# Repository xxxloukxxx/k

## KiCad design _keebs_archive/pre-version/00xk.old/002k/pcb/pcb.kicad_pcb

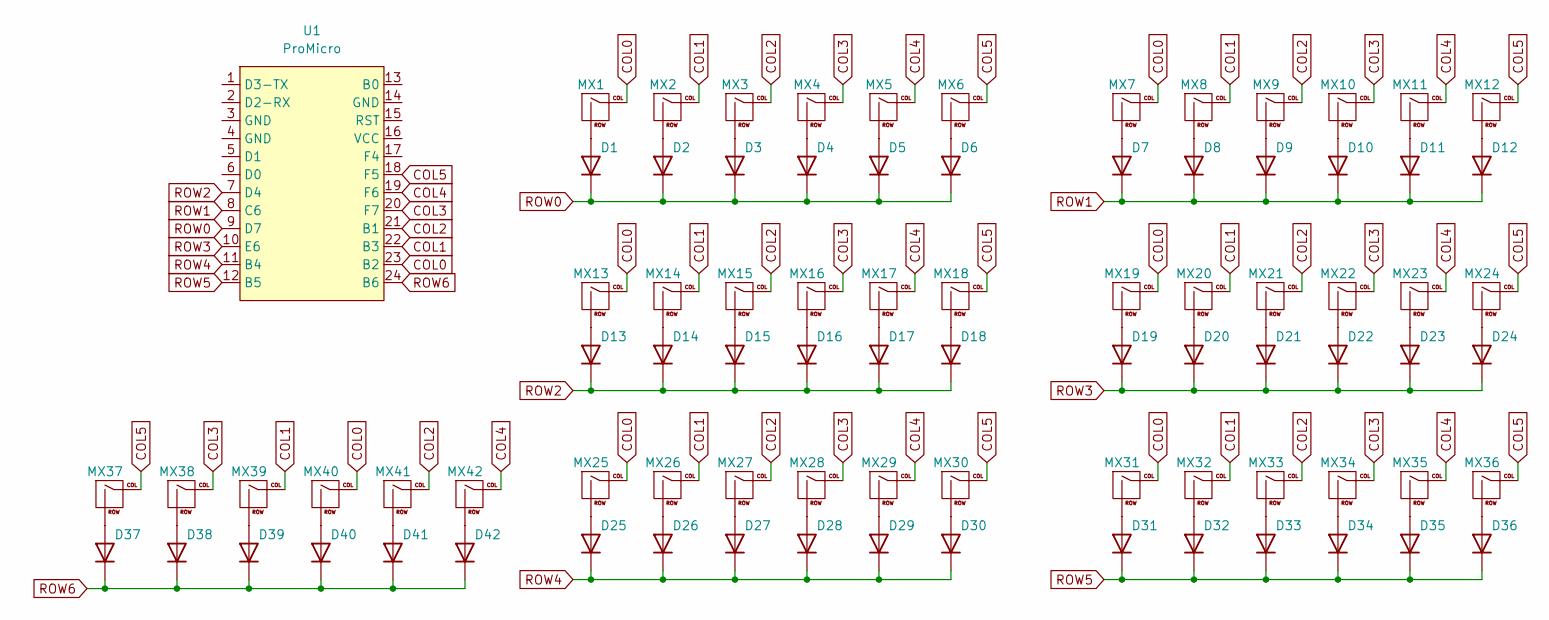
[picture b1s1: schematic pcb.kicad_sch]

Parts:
D1, D2, D3, D4, D5, D6, D7, D8, D9, D10, D11, D12, D13, D14, D15, D16, D17, D18, D19, D20, D21, D22, D23, D24, D25, D26, D27, D28, D29, D30, D31, D32, D33, D34, D35, D36, D37, D38, D39, D40, D41, D42: 1N4148; D_DO-35_SOD27_P7.62mm_Horizontal
MX1, MX2, MX3, MX4, MX5, MX6, MX7, MX8, MX9, MX10, MX11, MX12, MX13, MX14, MX15, MX16, MX17, MX18, MX19, MX20, MX21, MX22, MX23, MX24, MX25, MX26, MX27, MX28, MX29, MX30, MX31, MX32, MX33, MX34, MX35, MX36, MX37, MX42: MX; MX-Solderable-1U
MX38, MX39, MX40, MX41: MX; MX-Solderable-1.5U
U1: ProMicro; ProMicro_USBup

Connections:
COL0: MX1.1 (COL), MX7.1 (COL), MX13.1 (COL), MX19.1 (COL), MX25.1 (COL), MX31.1 (COL), MX40.1 (COL), U1.23 (B2)
COL1: MX2.1 (COL), MX8.1 (COL), MX14.1 (COL), MX20.1 (COL), MX26.1 (COL), MX32.1 (COL), MX39.1 (COL), U1.22 (B3)
COL2: MX3.1 (COL), MX9.1 (COL), MX15.1 (COL), MX21.1 (COL), MX27.1 (COL), MX33.1 (COL), MX41.1 (COL), U1.21 (B1)
COL3: MX4.1 (COL), MX10.1 (COL), MX16.1 (COL), MX22.1 (COL), MX28.1 (COL), MX34.1 (COL), MX38.1 (COL), U1.20 (F7)
COL4: MX5.1 (COL), MX11.1 (COL), MX17.1 (COL), MX23.1 (COL), MX29.1 (COL), MX35.1 (COL), MX42.1 (COL), U1.19 (F6)
COL5: MX6.1 (COL), MX12.1 (COL), MX18.1 (COL), MX24.1 (COL), MX30.1 (COL), MX36.1 (COL), MX37.1 (COL), U1.18 (F5)
unnamed: D1.2 (A), MX1.2 (ROW)
unnamed: D2.2 (A), MX2.2 (ROW)
unnamed: D3.2 (A), MX3.2 (ROW)
unnamed: D4.2 (A), MX4.2 (ROW)
unnamed: D5.2 (A), MX5.2 (ROW)
unnamed: D6.2 (A), MX6.2 (ROW)
unnamed: D7.2 (A), MX7.2 (ROW)
unnamed: D8.2 (A), MX8.2 (ROW)
unnamed: D9.2 (A), MX9.2 (ROW)
unnamed: D10.2 (A), MX10.2 (ROW)
unnamed: D11.2 (A), MX11.2 (ROW)
unnamed: D12.2 (A), MX12.2 (ROW)
unnamed: D13.2 (A), MX13.2 (ROW)
unnamed: D14.2 (A), MX14.2 (ROW)
unnamed: D15.2 (A), MX15.2 (ROW)
unnamed: D16.2 (A), MX16.2 (ROW)
unnamed: D17.2 (A), MX17.2 (ROW)
unnamed: D18.2 (A), MX18.2 (ROW)
unnamed: D19.2 (A), MX19.2 (ROW)
unnamed: D20.2 (A), MX20.2 (ROW)
unnamed: D21.2 (A), MX21.2 (ROW)
unnamed: D22.2 (A), MX22.2 (ROW)
unnamed: D23.2 (A), MX23.2 (ROW)
unnamed: D24.2 (A), MX24.2 (ROW)
unnamed: D25.2 (A), MX25.2 (ROW)
unnamed: D26.2 (A), MX26.2 (ROW)
unnamed: D27.2 (A), MX27.2 (ROW)
unnamed: D28.2 (A), MX28.2 (ROW)
unnamed: D29.2 (A), MX29.2 (ROW)
unnamed: D30.2 (A), MX30.2 (ROW)
unnamed: D31.2 (A), MX31.2 (ROW)
unnamed: D32.2 (A), MX32.2 (ROW)
unnamed: D33.2 (A), MX33.2 (ROW)
unnamed: D34.2 (A), MX34.2 (ROW)
unnamed: D35.2 (A), MX35.2 (ROW)
unnamed: D36.2 (A), MX36.2 (ROW)
unnamed: D37.2 (A), MX37.2 (ROW)
unnamed: D38.2 (A), MX38.2 (ROW)
unnamed: D39.2 (A), MX39.2 (ROW)
unnamed: D40.2 (A), MX40.2 (ROW)
unnamed: D41.2 (A), MX41.2 (ROW)
unnamed: D42.2 (A), MX42.2 (ROW)
ROW0: D1.1 (K), D2.1 (K), D3.1 (K), D4.1 (K), D5.1 (K), D6.1 (K), U1.9 (D7)
ROW1: D7.1 (K), D8.1 (K), D9.1 (K), D10.1 (K), D11.1 (K), D12.1 (K), U1.8 (C6)
ROW2: D13.1 (K), D14.1 (K), D15.1 (K), D16.1 (K), D17.1 (K), D18.1 (K), U1.7 (D4)
ROW3: D19.1 (K), D20.1 (K), D21.1 (K), D22.1 (K), D23.1 (K), D24.1 (K), U1.10 (E6)
ROW4: D25.1 (K), D26.1 (K), D27.1 (K), D28.1 (K), D29.1 (K), D30.1 (K), U1.11 (B4)
ROW5: D31.1 (K), D32.1 (K), D33.1 (K), D34.1 (K), D35.1 (K), D36.1 (K), U1.12 (B5)
ROW6: D37.1 (K), D38.1 (K), D39.1 (K), D40.1 (K), D41.1 (K), D42.1 (K), U1.24 (B6)

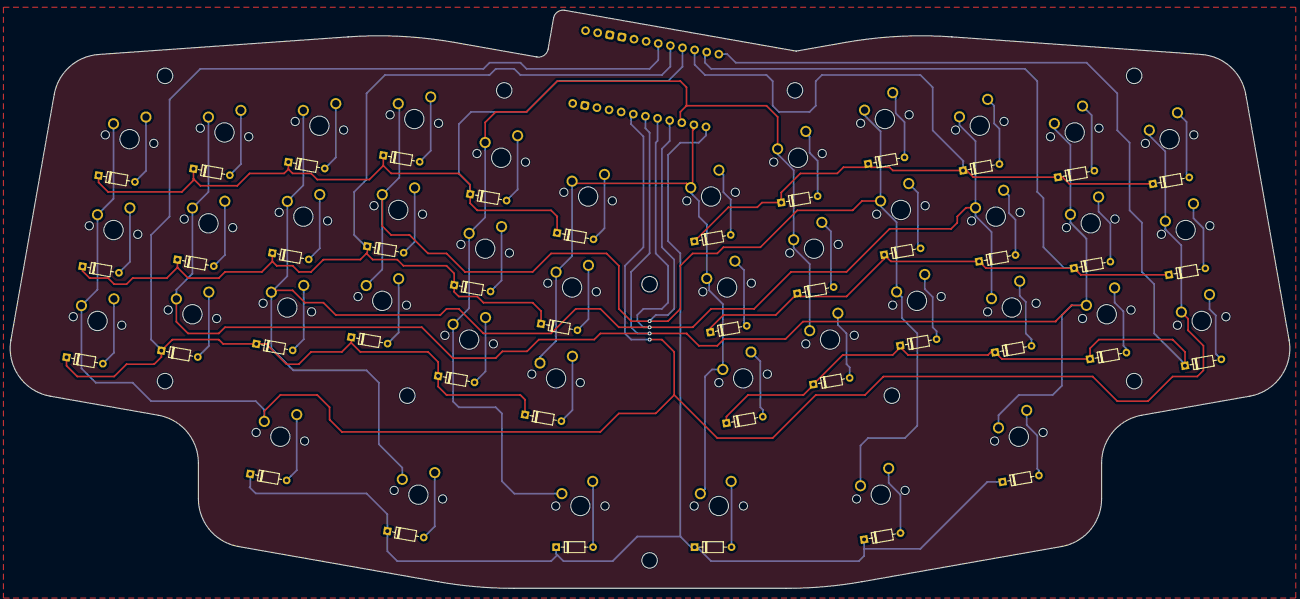
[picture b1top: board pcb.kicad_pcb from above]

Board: 2 copper layers, 264.1 x 119.3 mm, 95 parts (1 on the bottom side), 55 nets.

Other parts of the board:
REF01, REF02, REF03, REF04, REF05, REF06, REF07, REF08, REF09, REF10: MountingHole_3.2mm_M3

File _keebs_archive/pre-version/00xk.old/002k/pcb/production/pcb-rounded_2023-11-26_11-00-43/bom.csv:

Designator,Footprint,Quantity,Value,LCSC Part #
"D1, D10, D11, D12, D13, D14, D15, D16, D17, D18, D19, D2, D20, D21, D22, D23, D24, D25, D26, D27, D28, D29, D3, D30, D31, D32, D33, D34, D35, D36, D37, D38, D39, D4, D40, D41, D42, D5, D6, D7, D8, D9",D_DO-35_SOD27_P7.62mm_Horizontal,42,1N4148,
"MX1, MX10, MX11, MX12, MX13, MX14, MX15, MX16, MX17, MX18, MX19, MX2, MX20, MX21, MX22, MX23, MX24, MX25, MX26, MX27, MX28, MX29, MX3, MX30, MX31, MX32, MX33, MX34, MX35, MX36, MX37, MX4, MX42, MX5, MX6, MX7, MX8, MX9",MX-Solderable-1U,38,MX,
"MX38, MX39, MX40, MX41",MX-Solderable-1.5U,4,MX,

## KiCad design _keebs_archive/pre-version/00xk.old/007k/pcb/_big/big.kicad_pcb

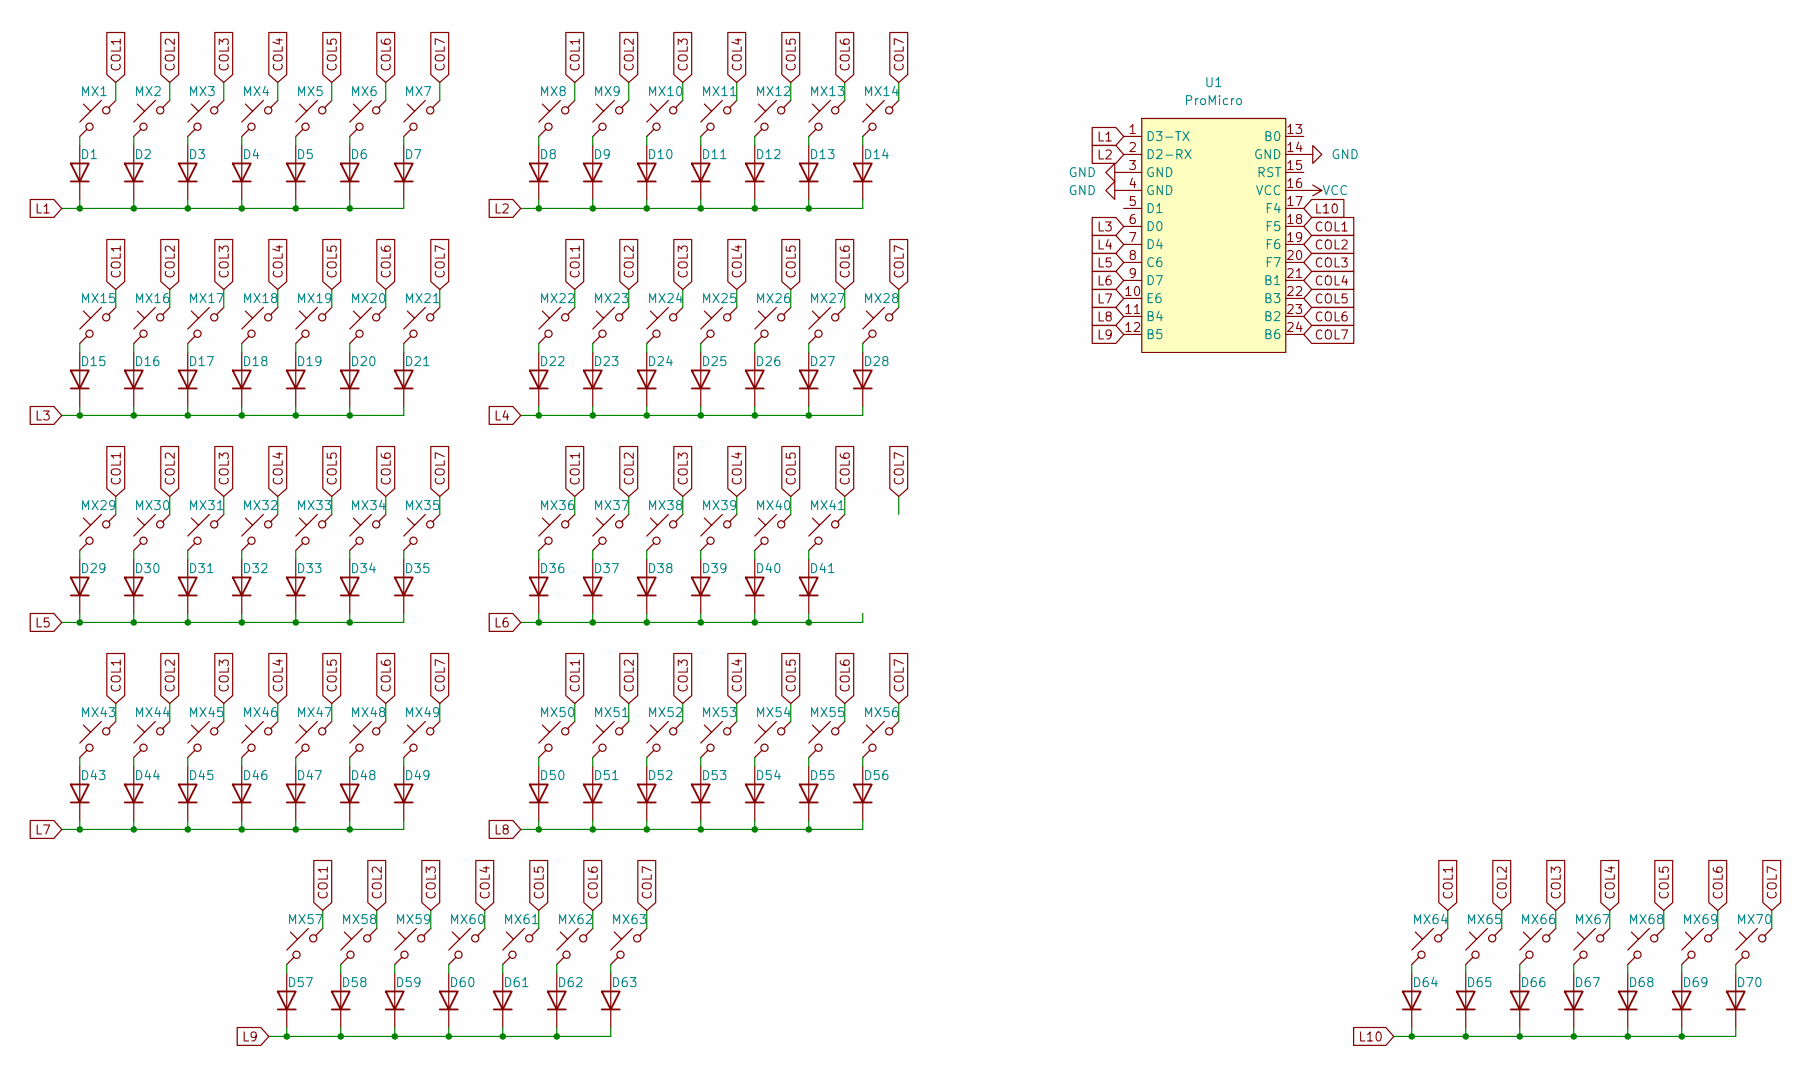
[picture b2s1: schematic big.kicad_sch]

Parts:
D1, D2, D3, D4, D5, D6, D7, D8, D9, D10, D11, D12, D13, D14, D15, D16, D17, D18, D19, D20, D21, D22, D23, D24, D25, D26, D27, D28, D29, D30, D31, D32, D33, D34, D35, D36, D37, D38, D39, D40, D41, D43, D44, D45, D46, D47, D48, D49, D50, D51, D52, D53, D54, D55, D56, D57, D58, D59, D60, D61, D62, D63, D64, D65, D66, D67, D68, D69, D70: 1N4148; D_DO-35_SOD27_P7.62mm_Horizontal
MX1, MX2, MX3, MX4, MX5, MX6, MX7, MX8, MX9, MX10, MX11, MX12, MX13, MX16, MX17, MX18, MX19, MX20, MX21, MX22, MX23, MX24, MX25, MX26, MX27, MX28, MX30, MX31, MX32, MX33, MX34, MX35, MX36, MX37, MX38, MX39, MX40, MX44, MX45, MX46, MX47, MX48, MX49, MX50, MX51, MX52, MX53, MX55, MX56, MX63, MX64, MX65, MX66, MX67, MX68, MX69, MX70: MX_SW_solder; MX-Alps-Hybrid-1U
MX14, MX15: MX_SW_solder; MX-Alps-Hybrid-1.5U
MX29, MX41, MX54: MX_SW_solder; MX-Alps-Hybrid-1.75U
MX43, MX62: MX_SW_solder; MX-Alps-Hybrid-2.25U
MX57, MX58, MX59, MX61: MX_SW_solder; MX-Alps-Hybrid-1.25U
MX60: MX_SW_solder; MX-Alps-Hybrid-2.75U
U1: ProMicro; ProMicro_USBup

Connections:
COL1: MX1.2, MX8.2, MX15.2, MX22.2, MX29.2, MX36.2, MX43.2, MX50.2, MX57.2, MX64.2, U1.18 (F5)
COL2: MX2.2, MX9.2, MX16.2, MX23.2, MX30.2, MX37.2, MX44.2, MX51.2, MX58.2, MX65.2, U1.19 (F6)
COL3: MX3.2, MX10.2, MX17.2, MX24.2, MX31.2, MX38.2, MX45.2, MX52.2, MX59.2, MX66.2, U1.20 (F7)
COL4: MX4.2, MX11.2, MX18.2, MX25.2, MX32.2, MX39.2, MX46.2, MX53.2, MX60.2, MX67.2, U1.21 (B1)
COL5: MX5.2, MX12.2, MX19.2, MX26.2, MX33.2, MX40.2, MX47.2, MX54.2, MX61.2, MX68.2, U1.22 (B3)
COL6: MX6.2, MX13.2, MX20.2, MX27.2, MX34.2, MX41.2, MX48.2, MX55.2, MX62.2, MX69.2, U1.23 (B2)
COL7: MX7.2, MX14.2, MX21.2, MX28.2, MX35.2, MX49.2, MX56.2, MX63.2, MX70.2, U1.24 (B6)
GND: U1.3 (GND), U1.4 (GND), U1.14 (GND)
L1: D1.1 (K), D2.1 (K), D3.1 (K), D4.1 (K), D5.1 (K), D6.1 (K), D7.1 (K), U1.1 (D3-TX)
L2: D8.1 (K), D9.1 (K), D10.1 (K), D11.1 (K), D12.1 (K), D13.1 (K), D14.1 (K), U1.2 (D2-RX)
L3: D15.1 (K), D16.1 (K), D17.1 (K), D18.1 (K), D19.1 (K), D20.1 (K), D21.1 (K), U1.6 (D0)
L4: D22.1 (K), D23.1 (K), D24.1 (K), D25.1 (K), D26.1 (K), D27.1 (K), D28.1 (K), U1.7 (D4)
L5: D29.1 (K), D30.1 (K), D31.1 (K), D32.1 (K), D33.1 (K), D34.1 (K), D35.1 (K), U1.8 (C6)
L6: D36.1 (K), D37.1 (K), D38.1 (K), D39.1 (K), D40.1 (K), D41.1 (K), U1.9 (D7)
L7: D43.1 (K), D44.1 (K), D45.1 (K), D46.1 (K), D47.1 (K), D48.1 (K), D49.1 (K), U1.10 (E6)
L8: D50.1 (K), D51.1 (K), D52.1 (K), D53.1 (K), D54.1 (K), D55.1 (K), D56.1 (K), U1.11 (B4)
L9: D57.1 (K), D58.1 (K), D59.1 (K), D60.1 (K), D61.1 (K), D62.1 (K), D63.1 (K), U1.12 (B5)
L10: D64.1 (K), D65.1 (K), D66.1 (K), D67.1 (K), D68.1 (K), D69.1 (K), D70.1 (K), U1.17 (F4)
unnamed: D1.2 (A), MX1.1
unnamed: D2.2 (A), MX2.1
unnamed: D3.2 (A), MX3.1
unnamed: D4.2 (A), MX4.1
unnamed: D5.2 (A), MX5.1
unnamed: D6.2 (A), MX6.1
unnamed: D7.2 (A), MX7.1
unnamed: D8.2 (A), MX8.1
unnamed: D9.2 (A), MX9.1
unnamed: D10.2 (A), MX10.1
unnamed: D11.2 (A), MX11.1
unnamed: D12.2 (A), MX12.1
unnamed: D13.2 (A), MX13.1
unnamed: D14.2 (A), MX14.1
unnamed: D15.2 (A), MX15.1
unnamed: D16.2 (A), MX16.1
unnamed: D17.2 (A), MX17.1
unnamed: D18.2 (A), MX18.1
unnamed: D19.2 (A), MX19.1
unnamed: D20.2 (A), MX20.1
unnamed: D21.2 (A), MX21.1
unnamed: D22.2 (A), MX22.1
unnamed: D23.2 (A), MX23.1
unnamed: D24.2 (A), MX24.1
unnamed: D25.2 (A), MX25.1
unnamed: D26.2 (A), MX26.1
unnamed: D27.2 (A), MX27.1
unnamed: D28.2 (A), MX28.1
unnamed: D29.2 (A), MX29.1
unnamed: D30.2 (A), MX30.1
unnamed: D31.2 (A), MX31.1
unnamed: D32.2 (A), MX32.1
unnamed: D33.2 (A), MX33.1
unnamed: D34.2 (A), MX34.1
unnamed: D35.2 (A), MX35.1
unnamed: D36.2 (A), MX36.1
unnamed: D37.2 (A), MX37.1
unnamed: D38.2 (A), MX38.1
unnamed: D39.2 (A), MX39.1
unnamed: D40.2 (A), MX40.1
unnamed: D41.2 (A), MX41.1
unnamed: D43.2 (A), MX43.1
unnamed: D44.2 (A), MX44.1
unnamed: D45.2 (A), MX45.1
unnamed: D46.2 (A), MX46.1
unnamed: D47.2 (A), MX47.1
unnamed: D48.2 (A), MX48.1
unnamed: D49.2 (A), MX49.1
unnamed: D50.2 (A), MX50.1
unnamed: D51.2 (A), MX51.1
unnamed: D52.2 (A), MX52.1
unnamed: D53.2 (A), MX53.1
unnamed: D54.2 (A), MX54.1
unnamed: D55.2 (A), MX55.1
unnamed: D56.2 (A), MX56.1
unnamed: D57.2 (A), MX57.1
unnamed: D58.2 (A), MX58.1
unnamed: D59.2 (A), MX59.1
unnamed: D60.2 (A), MX60.1
unnamed: D61.2 (A), MX61.1
unnamed: D62.2 (A), MX62.1
unnamed: D63.2 (A), MX63.1
unnamed: D64.2 (A), MX64.1
unnamed: D65.2 (A), MX65.1
unnamed: D66.2 (A), MX66.1
unnamed: D67.2 (A), MX67.1
unnamed: D68.2 (A), MX68.1
unnamed: D69.2 (A), MX69.1
unnamed: D70.2 (A), MX70.1
VCC: U1.16 (VCC)

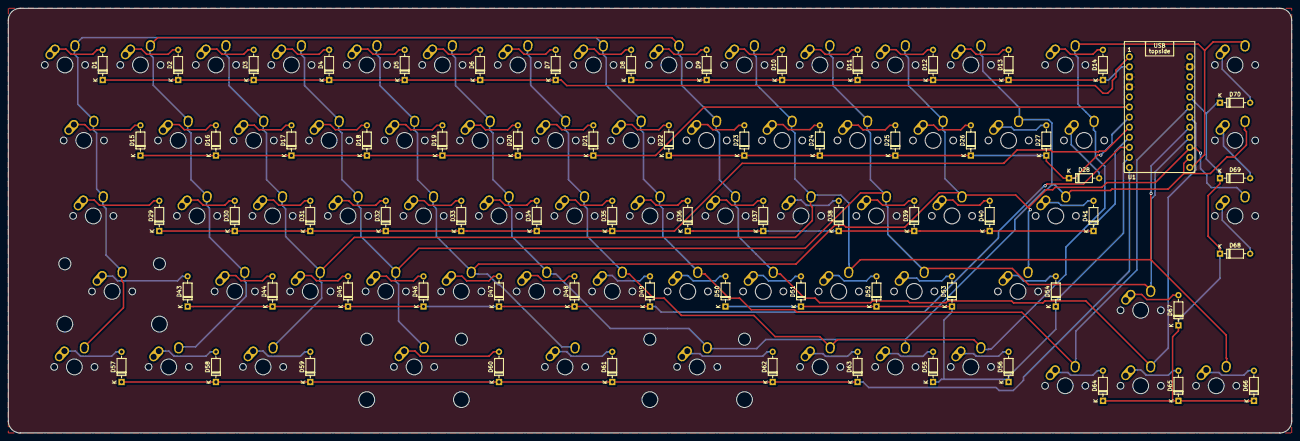
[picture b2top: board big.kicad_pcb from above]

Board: 2 copper layers, 323.9 x 107.2 mm, 139 parts (0 on the bottom side), 87 nets.
